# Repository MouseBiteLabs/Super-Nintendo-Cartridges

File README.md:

# Super Nintendo Game Cartridges

This is a repository listing all of my Super Nintendo Cartridge board variants. These *do not* include variants with special chips, such as SA-1 or the Super Game Boy boards. This repository is for the "standard" mapping types.

Use the following table (or navigate the above folders) for information on each specific baord type. <a href="https://github.com/MouseBiteLabs/Super-Nintendo-Cartridges/wiki">Please also review the wiki for more information.</a>

Note that the boards listed below are planned for development. No dates for upload are guaranteed.

## SNES Board Variants

| **Board Name**                                                                                                     | **Board Number**   | **Max ROM Size** | **Max RAM Size** | **Mappings Supported**         | **Multicart Support?**            | **Memory Family Used** |
|--------------------------------------------------------------------------------------------------------------------|--------------------|------------------|------------------|--------------------------------|-----------------------------------|------------------------|
| <a href="https://github.com/MouseBiteLabs/Super-Nintendo-Cartridges/tree/main/Advanced%20Flash">Advanced Flash</a> | SNES-8XJ4D-01A     | 8 MB             | 32 KB            | LoROM, HiROM, ExLoROM, ExHiROM | Yes (2 games; 4MB ROM, 32KB RAM)  | Type A (M29F160)       |
| <a href="https://github.com/MouseBiteLabs/Super-Nintendo-Cartridges/tree/main/LoROM%20Flash">LoROM Flash</a>       | SNES-8XL8D-01A     | 8 MB             | 128 KB           | LoROM, ExLoROM                 | Yes (2 games; 4MB ROM, 32KB RAM)  | Type A (M29F160)       |
| <a href="https://github.com/MouseBiteLabs/Super-Nintendo-Cartridges/tree/main/HiROM%20Flash">HiROM Flash</a>       | SNES-8XH8D-01A     | 8 MB             | 128 KB           | HiROM, ExHiROM                 | Yes (2 games; 4MB ROM, 32KB RAM)  | Type A (M29F160)       |
| <a href="https://github.com/MouseBiteLabs/Super-Nintendo-Cartridges/tree/main/Advanced%20UV">Advanced UV</a>       | SNES-8XJ8D-01C     | 8 MB             | 128 KB           | LoROM, HiROM, ExLoROM, ExHiROM | Yes (2 games; 4MB ROM, 32KB RAM)  | Type C (27C322)        |
| <a href="https://github.com/MouseBiteLabs/Super-Nintendo-Cartridges/tree/main/Basic%20UV">Basic UV</a>             | SNES-4NJ8D-01C     | 4 MB             | 128 KB           | LoROM, HiROM                   | No                                | Type C (27C160)        |
| <a href="https://github.com/MouseBiteLabs/Super-Nintendo-Cartridges/tree/main/SA-1">SA-1</a>                       | SNES-4SA8S-01C     | 4 MB             | 128 KB           | N/A                            | No                                | Type C (27C322)        |

## Naming Convention

| SNES                                | \- | 8                 | X               | J              | 4            | D                                    | \- | 01       | A                                       |
| ----------------------------------- | -- | ----------------- | --------------- | -------------- | ------------ | ------------------------------------ | -- | -------- | --------------------------------------- |
| Super Nintendo Entertainment System |    | Max ROM Size (MB) | Ex Mode Support | Mapper Type(s) | Max RAM Size | Multicart Support                    |    | Revision | Memory Family                           |
|                                     |    | 1                 | N = No          | L = LoROM      | 0 = None     | S = Single game                      |    |          | A = New EEPROM (M29F160)                |
|                                     |    | 2                 | X = Yes         | H = HiROM      | 1 = 2 KB     | D = Multicart (split max ROM space)  |    |          | B = NOS EEPROM (29F016, 29F032, 29F033) |
|                                     |    | 4                 |                 | J = Both       | 2 = 8 KB     | M = Multicart (double max ROM space) |    |          | C = UV EPROMs (27C160, 27C322, etc)     |
|                                     |    | 6                 | SA =            | SA1            | 4 = 32 KB    |                                      |    |          |                                         |
|                                     |    | 8                 |                 |                | 8 = 128 KB   |                                      |    |          |                                         |

## License

<br />This work is licensed under a <a rel="license" href="http://creativecommons.org/licenses/by-sa/4.0/">Creative Commons Attribution-ShareAlike 4.0 International License</a>. You are able to copy and redistribute the material in any medium or format, as well as remix, transform, or build upon the material for any purpose (even commercial) - but you **must** give appropriate credit, provide a link to the license, and indicate if any changes were made.

©MouseBiteLabs 2024

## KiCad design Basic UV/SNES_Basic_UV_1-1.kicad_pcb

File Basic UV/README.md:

# Super Nintendo Basic UV Cartridge (SNES-4NJ8D-01C) 

# Order at your own risk -- v1.1 is untested

This is an updated design of my old <a href="https://mousebitelabs.com/2019/08/12/how-to-make-a-snes-reproduction-cartridge-quick-guide/">SNES Basic cartridge boards</a>, which can use the original mask ROM chips from SNES carts, or the older 27C160 UV EPROM chips. You can even use my <a href="https://github.com/MouseBiteLabs/ROM-Adapter-Boards/tree/main/29F160%20to%20UV%20EPROM">29F160 to 27C160 adapter boards</a>, which use brand new 29F160 flash chips if you don't want to deal with old parts. 

Functionally, this design is the same as the older one, but under the hood I have ported the project over from Eagle to KiCad, and heavily cleaned up the schematic and some of the trace routings. I also added support for the MAD-1 chip from a donor board, unlocking a lot of potential for replacing old or damaged games. This version is also fully open source.

This cartridge covers a large portion of the SNES library, capable of any standard cartridge **but not those with co-processors, such as SA-1 or SuperFX.** You can backup games onto it with the following settings:
- HiROM and LoROM memory maps
- Up to 4 MB of ROM space
- Up to 128 KB of RAM space

All gerbers and source files can be found in this repo, as again, this project is fully open source. Please read all instructions before attempting the project.

## Important Things Before You Start

1) <a href="https://github.com/MouseBiteLabs/Super-Nintendo-Cartridges/wiki">Please review the wiki for more information about using the circuit boards, instructions for how to program them, and example builds.</a>
2) When soldering parts on, it's a good idea to put kapton tape or otherwise cover the bottom cartridge edge. You do not want to get solder on the cartridge contacts.
3) I am not responsible for any damage you do to your self or your property. Attempt this project at your own risk.
4) I do not guarantee design compatibility. You may encounter issues with certain games. There is also a chance I have made an error in the design or the BOM - if this is the case, I will do everything I can to address the problem as quickly as possible.
5) If you are using this board to make games other than for personal use, you must have permission from the originator to use and distribute any ROM images or other related material. You are responsible for making sure you adhere to any license requirements.

DO NOT use my circuit boards for profiting from stolen work - this especially includes homebrew content, ROM hacks, and using fan-made labels without permission from the originator. **Support ALL original creators!**

## Board Characteristics and Order Information

The zipped folder contains all the gerber files for this board. The following options **must** be chosen when ordering boards for yourself.

- Thickness: 1.2mm
- Surface Finish: ENIG
- Gold Fingers: Yes, 30° chamfer

You can use the zipped folder at any board fabricator you like. You may also buy the board from PCBWay using this link (disclosure: I receive 10% of the sale value to go towards future PCB orders of my own):

### Purchase from My Website

You can purchase this circuit board at my website, [https://mousebitelabs.store](https://mousebitelabs.store). Click the following image to be directed to the specific item listing:

### Purchase from Etsy

I also offer the board on Etsy, if you would rather purchase through there - click the banner to be redirected.

## Required Equipment

- You will need basic tools, like a soldering iron.
- If you are using this board with any OEM parts, like the CIC or MAD-1 or even a full replacement cartridge, you will... need that cartridge.
- If you are not using an original ROM chip, you need a way to program the new ROM chip. There are a few ways I have programmed them in the past:
  - You can use the <a href="https://xgecu.myshopify.com/products/xgecu-new-t48-tl866-3gprogrammer-v12-01-support-28000-ics-for-spi-nor-nand-flash-emmc-bga153-162-169-100-221-tsop-sop-plcc">T48 programmer</a> to program 27C801 or equivalent 1MB UV EPROMs for U3.
  - Using the T48 programmer with my <a href="https://github.com/MouseBiteLabs/27C322-TL866-Adapter">27C322 to TL866 Programming Adatper</a> board allows you to program 27C160 UV EPROMs.
  - The <a href="https://www.mcumall.com/store/index.php?route=product/product&path=66&product_id=85">GQ4x4 programmer</a> (and the ZIF adapter board that comes with it) can also be used to program UV EPROMs.
  - The T48 programmer with the <a href="https://xgecu.myshopify.com/products/100-original-xgecu-adp_f48_ex-1-tsop48-special-adapter-for-nor-flash-only-use-on-t48-tl866-3g-programmer">TSOP48 adapter</a> can be used to program 29F160 chips on my <a href="https://github.com/MouseBiteLabs/ROM-Adapter-Boards/tree/main/29F160%20to%20UV%20EPROM">29F160 to 27C160 adapter boards</a> placed in the U4 socket, or to program 29F016 chips on my <a href="https://github.com/MouseBiteLabs/ROM-Adapter-Boards/tree/main/SNES%20to%20TSOP">29F016 to SNES adapter boards</a> placed in the U3 socket.
  - If you are using the <a href="https://github.com/MouseBiteLabs/ROM-Adapter-Boards/tree/main/29F160%20to%20UV%20EPROM">29F160 to 27C160 adapter board</a>, and you install it into U4 along with the pin to connect /WE between the adapter and the cartridge, you can use the <a href="https://github.com/sanni/cartreader">OSCR</a> to load the game and save data onto the catridge, after the cartridge is assembled.
- This cartridge uses the PIC12F629 with the <a href="https://sd2snes.de/blog/cool-stuff/supercic">SuperCIC code</a> to fake out the lockout chip. You will need a way to program these PIC chips. I use the T48 to do so, but you can also use something like the <a href="https://www.microchip.com/en-us/development-tool/pg164130">PICkit 3.</a> Note that if you have region modded your SNES, you won't need the lockout chips in the cartridges.

## How to Program

<a href="https://github.com/MouseBiteLabs/Super-Nintendo-Cartridges/wiki/Preparing-the-ROM">Please check out the wiki pages on how to prepare the ROM and program the cartridge.</a>

### Important note for 27C801

If you are using a UV EPROM in the U3 socket (likely the 27C801), then the ROM file you load onto the chip must be swapbinned. This is covered in the wiki link above.

## Board Configurations

This board is highly customizable. You *do not* need every single part on this board to make a game. The game you want to make is mainly dependent on the memory mapping (LoROM/HiROM), the ROM size, and the RAM size. Depending on your needs, you only need to solder on certain components, which you can find below in the BOM section. You will also need to configure the game with the various solder jumpers on the back of the board.

<a href="https://github.com/MouseBiteLabs/Super-Nintendo-Cartridges/wiki/Basic-UV">**I highly recommend checking out the various examples of board configurations on the wiki.**</a>

### Components Required

I've split up the requisite parts into a few different "Groups" which you can find a comprehensive list for in the BOM section a few sections down from this one.

- **Every board needs Group A components.** You can make games that have no RAM and are up to 4 MB large with this configuration.
- If you need battery-backed RAM, **add Group B components.** This will add up to 128 KB of RAM space. You will then need to add either...
  - **Group C components** if you are using the 74HCT139 decoder chip (which does not require a donor cartridge),
 
  OR
  
  - **Group D components** if you are using the MAD-1 mapper (which requires a donor cartridge).

Along with these groups, please also follow the configurations detailed in the following sections.

### The Lockout Chip

There are two sockets and two capacitors labeled "U2" and "C2," respectively. Only populate ONE set of these. Do not populate both. The 16-pin socket is for the original CIC chip from a donor cartridge, and the 8-pin socket is for the SuperCIC clone chip using the PIC12F629 that you have to program yourself. If your SNES is modded to be region-unlocked, then you don't need either of these chips.

### Hi/Lo Socket Selection

If your game is the LoROM mapping type, solder U3 or U4 in the bottom set of sockets (labeled "LO" on the left side) and, if necessary, U6L or U8L. If your game is of the HiROM mapping type, solder U3 or U4 in the top set of sockets (labeled "HI" on the left side) and, if necessary, U6H or U8H.

### Mapper Bypass Solder Jumper

This is the only set of solder jumper pads on the front of the board. If your game does not use SRAM, then you must solder these pads together. **Do not solder these pads if your game uses SRAM.**

### LoRom/HiROM Solder Jumpers

For these 3-segment pads, use a solder bridge on the middle pad to either side depending on the option you need. There are a handful of them across the board, and not all of them are necessary for you to set - though, importantly, if you want to take the guesswork out of it, **you can configure all of them without any ill side effects** to make it simpler.

1) The one Lo/Hi jumper on the bottom left of the board, behind U3, only need to be set if you have a ROM in the U3 socket.
2) The two Lo/Hi jumpers on the right side, behind U6L and U6H (the MAD-1s), only need to be set if you are using U8L or U8L (the 74HCT139s)
3) The four Lo/Hi jumpers at the top of the board only need to be set if you are using SRAM on the board
4) The one Lo/Hi jumper in the middle of the board behind U4 only needs to be set if you are using the <a href="https://github.com/MouseBiteLabs/ROM-Adapter-Boards/tree/main/29F160%20to%20UV%20EPROM">29F160 to 27C160 adapter boards</a> in the U4 socket

### SRAM Size

The set of pads at the top left underneath the SRAM chip configure the size of the SRAM that the SNES will see. All pads must be configured if you are using SRAM, and each set of 2 should be soldered in the same direction. The example picture below shows a game configured for 256 Kbit of SRAM. **It is important to note these numbers represent the SRAM in BITS, not BYTES. To figure out the BYTES of SRAM, take the numbers here and divide by 8.**

### U4 Configuration Pads

These two sets of 3-way jumpers only need to be set if you have something populated in U4. Solder the middle pads to the left if you are using a 27C160 UV EPROM, or solder the middle pads to the right if you are using my <a href="https://github.com/MouseBiteLabs/ROM-Adapter-Boards/tree/main/29F160%20to%20UV%20EPROM">29F160 to 27C160 adapter boards</a>.

(Remember: the LoROM/HiROM pads to the right of these do not need to be set if you are using the 27C160.)

## Estimating Battery Life

To accurately estimate the battery life, measure the voltage across R1 using a multimeter in DC mV mode, touching the probes to the two test point pads on either side of R1. You should read something around 1 mV or less. If you are severely higher than 10 mV, like in the 100's of mV, then you have a problem on your board.

Once you have a suitable voltage, find the milliamp-hour rating of your selected battery (preferrably from a datasheet). For example, a Renata CR2032 battery is rated for 225 mAh.

Now to estimate battery life, take the voltage measurement in mV and the battery rating in mAh, and plug it into this equation: 

Time (years) = Resistance of R1 (ohms) * Battery capacity (mAh) / Voltage (mV) / 8760

The factor of 8760 is for converting years to hours (24 hours in a day, 365 days in a year). The resistance of R1 is 1000 ohms. So for an example, if you measured 1 mV on R1 and are using a Renata CR2032, you would get 1000 * 225 / 1 / 8760 = **25.7 years.**

## Troubleshooting

<a href="https://github.com/MouseBiteLabs/Super-Nintendo-Cartridges/wiki/Troubleshooting-Tips">Please check out the wiki pages for troubleshooting tips.</a>

## Bill of Materials (BOM)

The component groups required for the build you want to make are detailed above.

### Group A - Up to 4 MB ROM, No RAM

In the following table, choose **one** of the options for U2.

| Reference | Value/Part Number | Package              | Description                     | Source                                           |
| --------- | ----------------- | -------------------- | ------------------------------- | ------------------------------------------------ |
| C1        | 22u               | Radial 2.5mm spacing | Aluminum Electrolytic Capacitor | [https://mou.sr/4lzfiK1](https://mou.sr/4lzfiK1) |
| C2        | 0.1u              | Radial 2.5mm spacing | Ceramic Capacitor               | [https://mou.sr/481ILov](https://mou.sr/481ILov) |
| U2        | CIC               | DIP-16               | Region Lockout Chip             | Donor cartridge                                  |
| U2        | PIC12F629         | DIP-8                | PIC Microcontroller             | [https://mou.sr/3XuEZzO](https://mou.sr/3XuEZzO) |
| U2        | PIC12F629         | SOIC-8               | PIC Microcontroller             | [https://mou.sr/4dSUh90](https://mou.sr/4dSUh90) |

In the following table, choose **one** of the following options for U3 or U4. If you use a part in U3, then populate C3. If you use a part in U4, populate C4.

| Reference | Value/Part Number      | Package              | Description              | Source                                                                                                                                                                           |
| --------- | ---------------------- | -------------------- | ------------------------ | -------------------------------------------------------------------------------------------------------------------------------------------------------------------------------- |
| C3        | 0.1u                   | Radial 2.5mm spacing | Ceramic Capacitor        | [https://mou.sr/481ILov](https://mou.sr/481ILov)                                                                                                                                 |
| C4        | 0.1u                   | Radial 2.5mm spacing | Ceramic Capacitor        | [https://mou.sr/481ILov](https://mou.sr/481ILov)                                                                                                                                 |
| U3        | Mask ROM               | DIP-32/DIP-36        | Original SNES Mask ROM   | Donor Cartridge                                                                                                                                                                  |
| U3        | 27C801                 | DIP-32               | UV EPROM                 | AliExpress, eBay                                                                                                                                                                 |
| U3        | SNES-to-TSOP PCB       | DIP-36               | Adapter board for 29F016 | [https://github.com/MouseBiteLabs/ROM-Adapter-Boards/tree/main/SNES%20to%20TSOP](https://github.com/MouseBiteLabs/ROM-Adapter-Boards/tree/main/SNES%20to%20TSOP)                 |
| U4        | 27C160                 | DIP-42               | UV EPROM                 | AliExpress, eBay                                                                                                                                                                 |
| U4        | 29F160 to UV EPROM PCB | DIP-42               | Adapter board for 29F160 | [https://github.com/MouseBiteLabs/ROM-Adapter-Boards/tree/main/29F160%20to%20UV%20EPROM](https://github.com/MouseBiteLabs/ROM-Adapter-Boards/tree/main/29F160%20to%20UV%20EPROM) |

### Group B - adds 32 KB of RAM

| Reference | Value/Part Number | Package              | Description                     | Source                                           |
| --------- | ----------------- | -------------------- | ------------------------------- | ------------------------------------------------ |
| B1        | CR2032            | CR2032               | Coin Cell Battery               | [https://mou.sr/3Wj2m0G](https://mou.sr/3Wj2m0G) |
| CB        | 22u               | Radial 2.5mm spacing | Aluminum Electrolytic Capacitor | [https://mou.sr/4lzfiK1](https://mou.sr/4lzfiK1) |
| C5        | 0.1u              | Radial 2.5mm spacing | Ceramic Capacitor               | [https://mou.sr/481ILov](https://mou.sr/481ILov) |
| R1        | 1k                | Axial                | Resistor                        | [https://mou.sr/4hYkrZr](https://mou.sr/4hYkrZr) |
| U5        | AS6C62256         | DIP-28               | SRAM                            | [https://mou.sr/3HlZ0mh](https://mou.sr/3HlZ0mh) |

### Group B (Optional) - adds 128 KB of RAM (instead of 32 KB)

Replace U5 in Group B above with the part detailed here, and add the other three components. **I personally recommend sticking to the AS6C62256 SRAM chip unless you absolutely need more RAM space.**

| Reference | Value/Part Number | Package | Description | Source                                           |
| --------- | ----------------- | ------- | ----------- | ------------------------------------------------ |
| Q2        | 2N3904            | TO-92-3 | NPN BJT     | [https://mou.sr/3HlkU91](https://mou.sr/3HlkU91) |
| R6        | 100k              | Axial   | Resistor    | [https://mou.sr/3Ib4SgO](https://mou.sr/3Ib4SgO) |
| R7        | 10k               | Axial   | Resistor    | [https://mou.sr/42AN0WU](https://mou.sr/42AN0WU) |
| U5        | AS6C1008          | DIP-32  | SRAM        | [https://mou.sr/3hNkGxg](https://mou.sr/3hNkGxg) |

### Group C - adds supporting circuitry for battery backed RAM (no donor cart)

| Reference | Value/Part Number | Package              | Description       | Source                                                   |
| --------- | ----------------- | -------------------- | ----------------- | -------------------------------------------------------- |
| C8        | 0.1u              | Radial 2.5mm spacing | Ceramic Capacitor | [https://mou.sr/481ILov](https://mou.sr/481ILov)         |
| D1        | BAT85             | DO-35-2              | Schottky Diode    | [https://mou.sr/49GVT4m](https://mou.sr/49GVT4m)         |
| D2        | BAT85             | DO-35-2              | Schottky Diode    | [https://mou.sr/49GVT4m](https://mou.sr/49GVT4m)         |
| D3        | BAT85             | DO-35-2              | Schottky Diode    | [https://mou.sr/49GVT4m](https://mou.sr/49GVT4m)         |
| Q1        | 2N3904            | TO-92-3 / SOT-23-3   | NPN BJT           | THT: https://mou.sr/3HlkU91, SMT: https://mou.sr/3C8piaZ |
| R2        | 100k              | Axial                | Resistor          | [https://mou.sr/3Ib4SgO](https://mou.sr/3Ib4SgO)         |
| R3        | 10k               | Axial                | Resistor          | [https://mou.sr/42AN0WU](https://mou.sr/42AN0WU)         |
| R4        | 1k                | Axial                | Resistor          | [https://mou.sr/4hYkrZr](https://mou.sr/4hYkrZr)         |
| R5        | 10k               | Axial                | Resistor          | [https://mou.sr/42AN0WU](https://mou.sr/42AN0WU)         |
| U8        | 74HCT139          | DIP-16               | Decoder           | [https://mou.sr/441VXuJ](https://mou.sr/441VXuJ)         |

### Group D - adds supporting circuitry for battery backed RAM (donor cart)

| Reference | Value/Part Number | Package              | Description            | Source                                           |
| --------- | ----------------- | -------------------- | ---------------------- | ------------------------------------------------ |
| C6        | 0.1u              | Radial 2.5mm spacing | Ceramic Capacitor      | [https://mou.sr/481ILov](https://mou.sr/481ILov) |
| U6        | MAD-1             | DIP-16               | Memory Address Decoder | Donor Cartridge                                  |

## Restrictions for v1.0

If you have a v1.0 board, you have the following restrictions:

- Only a replacement CIC chip with the PIC12F629 can be used
- MAD-1 is not supported (the wiring is wrong)
- If you are using a 27C160 EPROM in U4, you must bend up pin 32 and separately wire it to a GND point (like pin 31 on the EPROM)

## Revision History

### v1.1 - Release

- Fix OEM CIC wiring
- Fix MAD-1 wiring
- Add jumpers and extra pins for 29F160 Adapter board support

### v1.0 - Prototype

- Release of the KiCad-ported version of my original SNES Basic cart design
- Removed the "SRAM Enable" pads and made the SRAM always enabled
- Added MAD-1 support to the board

## Acknowledgements

- Continual thanks to all in the nesdev community for their resources, design tips, and support throughout the past half-decade. This design was one of my original ones that was improved through their help and feedback when I was first starting out.

## License

<br />This work is licensed under a <a rel="license" href="http://creativecommons.org/licenses/by-sa/4.0/">Creative Commons Attribution-ShareAlike 4.0 International License</a>. You are able to copy and redistribute the material in any medium or format, as well as remix, transform, or build upon the material for any purpose (even commercial) - but you **must** give appropriate credit, provide a link to the license, and indicate if any changes were made.

©MouseBiteLabs 2025

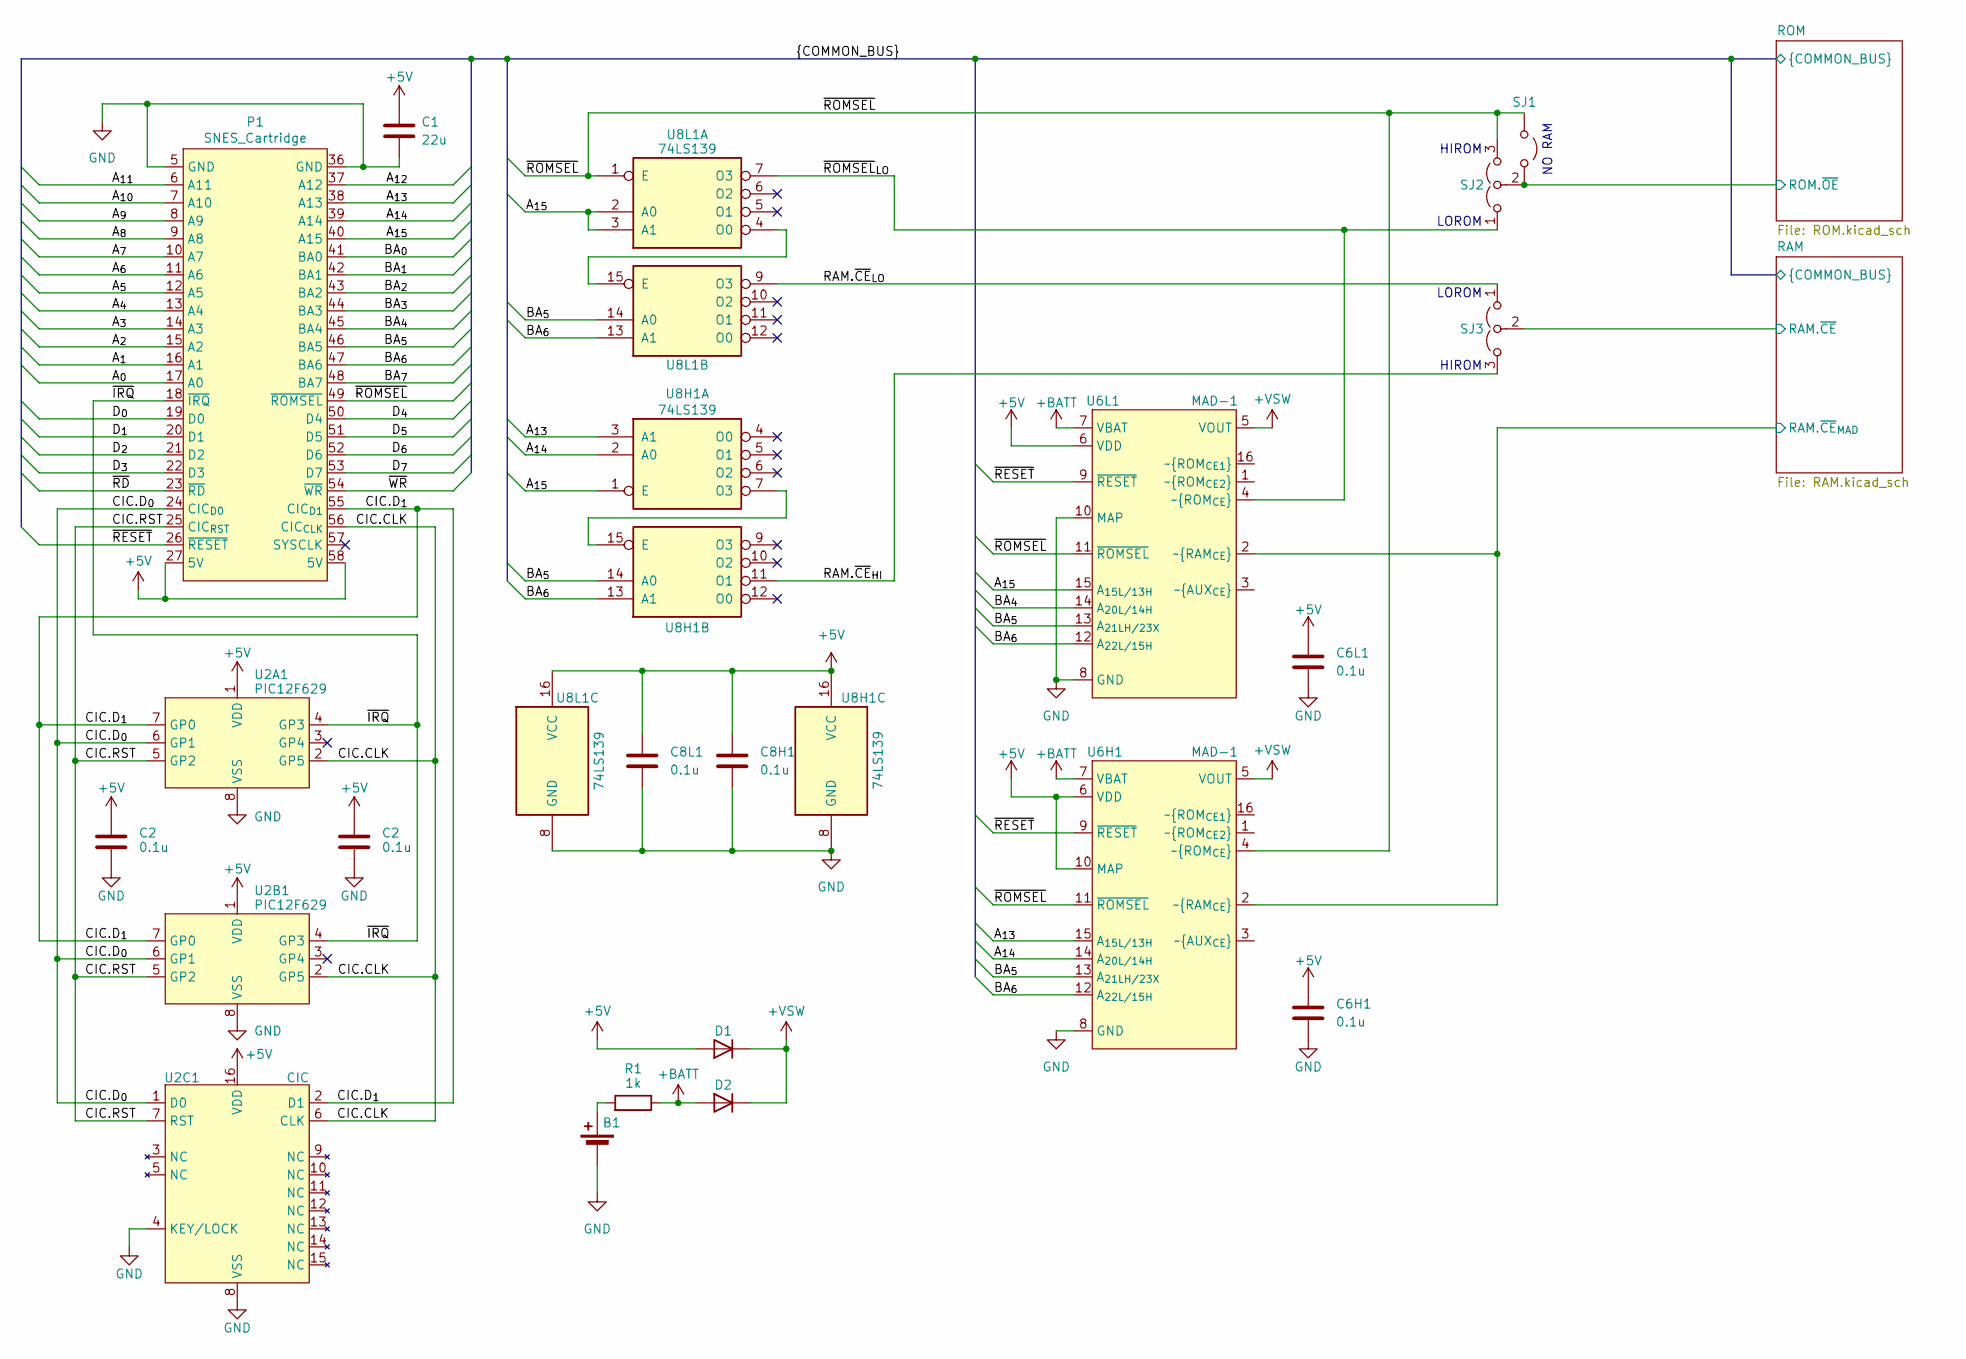
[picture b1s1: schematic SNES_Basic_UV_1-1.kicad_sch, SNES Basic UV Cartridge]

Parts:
B1: CR2025; COIN_CELL
C1: 22u; CP_Radial_D5.0mm_P2.50mm
C2, C6H1, C6L1, C8H1, C8L1: 0.1u; C_THT
D1, D2: D; DIODE_THT_SMT
P1: SNES_Cartridge; Cart_Edge_SNES_Standard
R1: 1k; THT_SMT_0803
SJ1: Jumper_2_Open; SJ
SJ2, SJ3: Jumper_3_Open; SJ_2
U2A1: PIC12F629; SOIC-8_3.9x4.9mm_P1.27mm
U2B1: PIC12F629; DIP-8_W7.62mm
U2C1: CIC; DIP-16_W7.62mm
U6H1, U6L1: MAD-1; DIP-16_W7.62mm
U8H1, U8L1: 74LS139; DIP-16_W7.62mm

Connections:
+5V: C1.1, C2.1, C6H1.1, C6L1.1, C8H1.1, C8L1.1, D1.2 (A), P1.27 (5V), P1.58 (5V), U2A1.1 (VDD), U2B1.1 (VDD), U2C1.16 (VDD), U6H1.6 (VDD), U6H1.10 (MAP), U6L1.6 (VDD), U8H1.16 (VCC), U8L1.16 (VCC); also elsewhere on the board
+BATT: D2.2 (A), R1.1, U6H1.7 (VBAT), U6L1.7 (VBAT)
+VSW: D1.1 (K), D2.1 (K), U6H1.5 (VOUT), U6L1.5 (VOUT); also elsewhere on the board
/A_{0}: P1.17 (A0); also elsewhere on the board
/A_{1}: P1.16 (A1); also elsewhere on the board
/A_{2}: P1.15 (A2); also elsewhere on the board
/A_{3}: P1.14 (A3); also elsewhere on the board
/A_{4}: P1.13 (A4); also elsewhere on the board
/A_{5}: P1.12 (A5); also elsewhere on the board
/A_{6}: P1.11 (A6); also elsewhere on the board
/A_{7}: P1.10 (A7); also elsewhere on the board
/A_{8}: P1.9 (A8); also elsewhere on the board
/A_{9}: P1.8 (A9); also elsewhere on the board
/A_{10}: P1.7 (A10); also elsewhere on the board
/A_{11}: P1.6 (A11); also elsewhere on the board
/A_{12}: P1.37 (A12); also elsewhere on the board
/A_{13}: P1.38 (A13), U6H1.15 (A_{15L/13H}), U8H1.3 (A1); also elsewhere on the board
/A_{14}: P1.39 (A14), U6H1.14 (A_{20L/14H}), U8H1.2 (A0); also elsewhere on the board
/A_{15}: P1.40 (A15), U6L1.15 (A_{15L/13H}), U8H1.1 (E), U8L1.2 (A0), U8L1.3 (A1); also elsewhere on the board
/BA_{0}: P1.41 (BA0); also elsewhere on the board
/BA_{1}: P1.42 (BA1); also elsewhere on the board
/BA_{2}: P1.43 (BA2); also elsewhere on the board
/BA_{3}: P1.44 (BA3); also elsewhere on the board
/BA_{4}: P1.45 (BA4), U6L1.14 (A_{20L/14H}); also elsewhere on the board
/BA_{5}: P1.46 (BA5), U6H1.13 (A_{21LH/23X}), U6L1.13 (A_{21LH/23X}), U8H1.14 (A0), U8L1.14 (A0); also elsewhere on the board
/BA_{6}: P1.47 (BA6), U6H1.12 (A_{22L/15H}), U6L1.12 (A_{22L/15H}), U8H1.13 (A1), U8L1.13 (A1); also elsewhere on the board
/BA_{7}: P1.48 (BA7); also elsewhere on the board
/CIC.CLK: P1.56 (CIC_{CLK}), U2A1.2 (GP5), U2B1.2 (GP5), U2C1.6 (CLK)
/CIC.D_{0}: P1.24 (CIC_{D0}), U2A1.6 (GP1), U2B1.6 (GP1), U2C1.1 (D0)
/CIC.D_{1}: P1.55 (CIC_{D1}), U2A1.7 (GP0), U2B1.7 (GP0), U2C1.2 (D1)
/CIC.RST: P1.25 (CIC_{RST}), U2A1.5 (GP2), U2B1.5 (GP2), U2C1.7 (RST)
/D_{0}: P1.19 (D0); also elsewhere on the board
/D_{1}: P1.20 (D1); also elsewhere on the board
/D_{2}: P1.21 (D2); also elsewhere on the board
/D_{3}: P1.22 (D3); also elsewhere on the board
/D_{4}: P1.50 (D4); also elsewhere on the board
/D_{5}: P1.51 (D5); also elsewhere on the board
/D_{6}: P1.52 (D6); also elsewhere on the board
/D_{7}: P1.53 (D7); also elsewhere on the board
/RAM.~CE_{HI}: SJ3.3 (B), U8H1.11 (O1)
/RAM.~CE_{LO}: SJ3.1 (A), U8L1.9 (O3)
/RAM/RAM.~CE: SJ3.2 (C); also elsewhere on the board
/RAM/~CE_{SRAM}: U6H1.2 (~RAM_{CE}), U6L1.2 (~RAM_{CE}); also elsewhere on the board
/ROM/ROM.~OE: SJ1.1 (A), SJ2.2 (C); also elsewhere on the board
/~IRQ: P1.18 (~IRQ), U2A1.4 (GP3), U2B1.4 (GP3)
/~RD: P1.23 (~RD); also elsewhere on the board
/~RESET: P1.26 (~RESET), U6H1.9 (~RESET), U6L1.9 (~RESET); also elsewhere on the board
/~ROMSEL: P1.49 (~ROMSEL), SJ1.2 (B), SJ2.3 (B), U6H1.4 (~ROM_{CE}), U6H1.11 (~ROMSEL), U6L1.11 (~ROMSEL), U8L1.1 (E)
/~ROMSEL_{LO}: SJ2.1 (A), U6L1.4 (~ROM_{CE}), U8L1.7 (O3)
/~WR: P1.54 (~WR); also elsewhere on the board
GND: B1.2 (-), C1.2, C2.2, C6H1.2, C6L1.2, C8H1.2, C8L1.2, P1.5 (GND), P1.36 (GND), U2A1.8 (VSS), U2B1.8 (VSS), U2C1.4 (KEY/LOCK), U2C1.8 (VSS), U6H1.8 (GND), U6L1.8 (GND), U6L1.10 (MAP), U8H1.8 (GND), U8L1.8 (GND); also elsewhere on the board
unnamed: B1.1 (+), R1.2
unnamed: U8H1.7 (O3), U8H1.15 (E)
unnamed: U8L1.4 (O0), U8L1.15 (E)

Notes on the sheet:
HIROM LOROM
NO RAM
LOROM HIROM

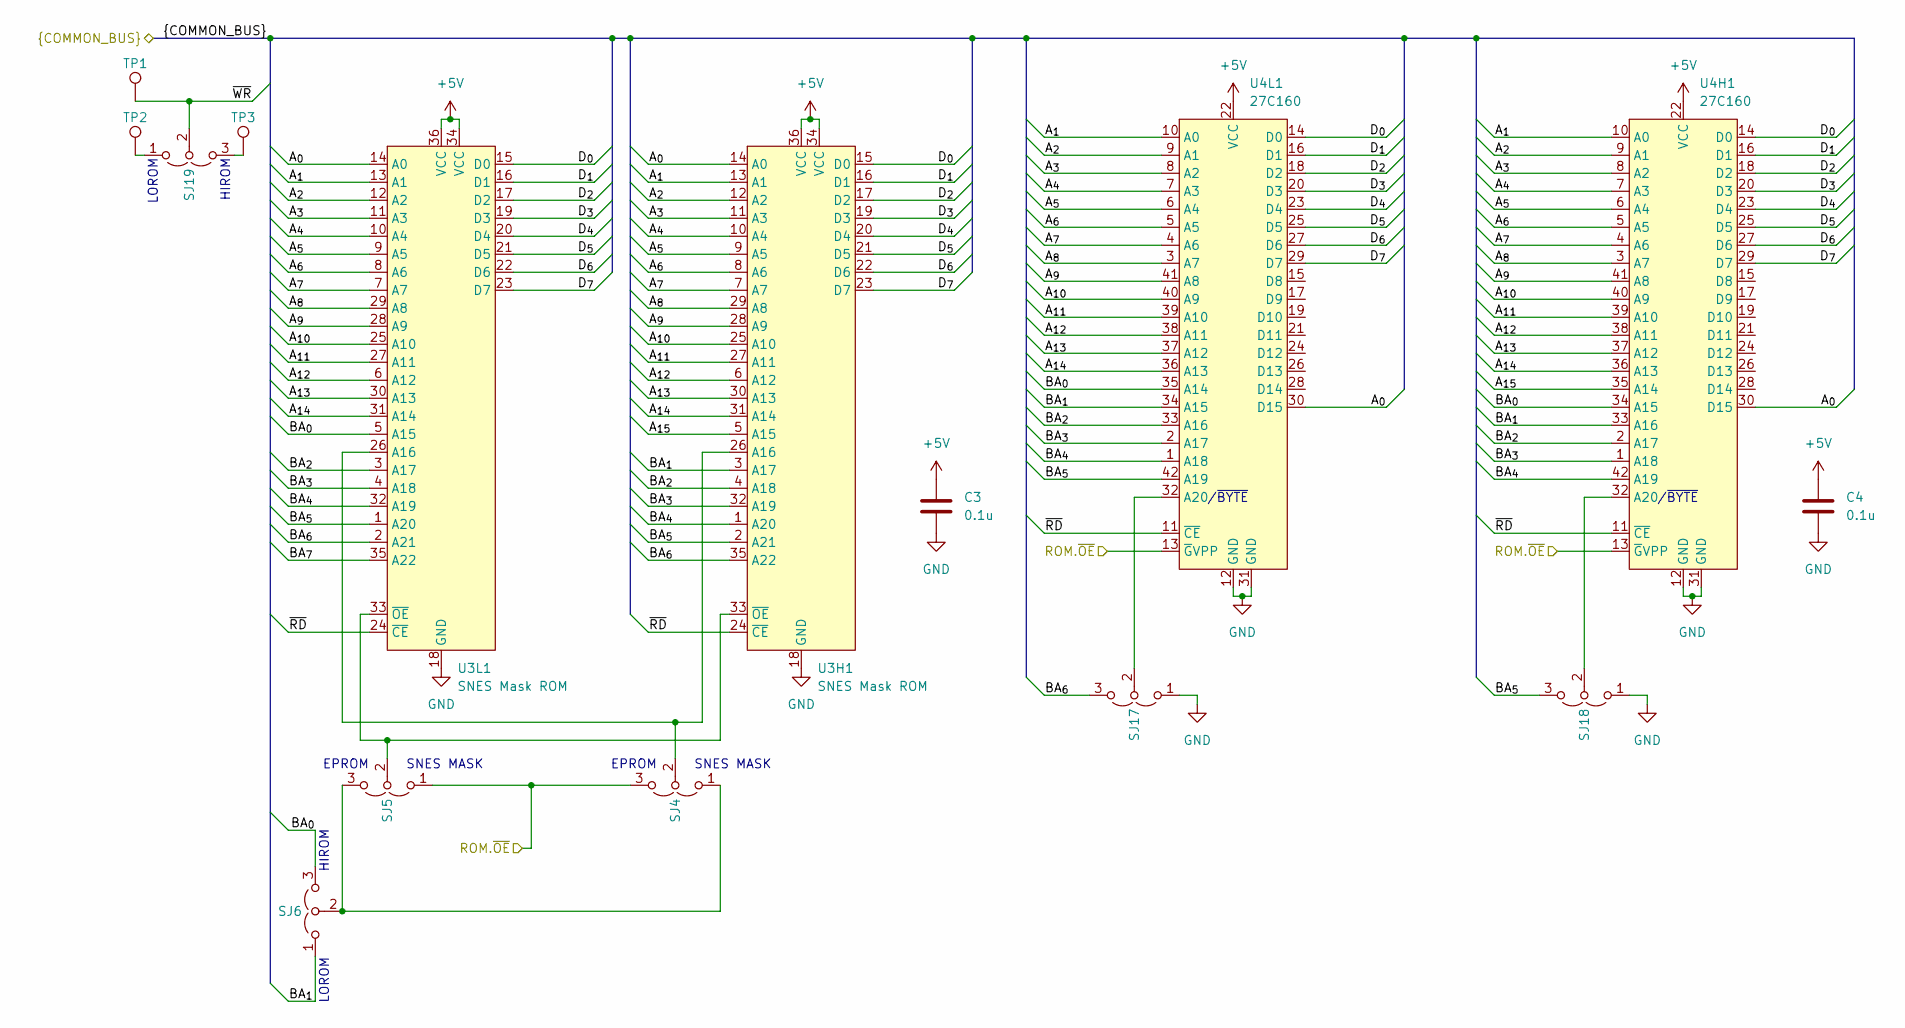
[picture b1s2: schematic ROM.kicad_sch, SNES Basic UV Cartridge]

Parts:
C3, C4: 0.1u; C_THT
SJ4, SJ5, SJ6, SJ17, SJ18, SJ19: Jumper_3_Open; SJ_2
TP1, TP2, TP3: TPB1,27; TestPoint_THTPad_D1.5mm_Drill0.7mm
U3H1, U3L1: SNES Mask ROM; 36-PDIP_SLIM
U4H1, U4L1: 27C160; DIP-42_W15.24mm

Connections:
+5V: C3.1, C4.1, U3H1.34 (VCC), U3H1.36 (VCC), U3L1.34 (VCC), U3L1.36 (VCC), U4H1.22 (VCC), U4L1.22 (VCC); also elsewhere on the board
/A_{0}: U3H1.14 (A0), U3L1.14 (A0), U4H1.30 (D15), U4L1.30 (D15); also elsewhere on the board
/A_{1}: U3H1.13 (A1), U3L1.13 (A1), U4H1.10 (A0), U4L1.10 (A0); also elsewhere on the board
/A_{2}: U3H1.12 (A2), U3L1.12 (A2), U4H1.9 (A1), U4L1.9 (A1); also elsewhere on the board
/A_{3}: U3H1.11 (A3), U3L1.11 (A3), U4H1.8 (A2), U4L1.8 (A2); also elsewhere on the board
/A_{4}: U3H1.10 (A4), U3L1.10 (A4), U4H1.7 (A3), U4L1.7 (A3); also elsewhere on the board
/A_{5}: U3H1.9 (A5), U3L1.9 (A5), U4H1.6 (A4), U4L1.6 (A4); also elsewhere on the board
/A_{6}: U3H1.8 (A6), U3L1.8 (A6), U4H1.5 (A5), U4L1.5 (A5); also elsewhere on the board
/A_{7}: U3H1.7 (A7), U3L1.7 (A7), U4H1.4 (A6), U4L1.4 (A6); also elsewhere on the board
/A_{8}: U3H1.29 (A8), U3L1.29 (A8), U4H1.3 (A7), U4L1.3 (A7); also elsewhere on the board
/A_{9}: U3H1.28 (A9), U3L1.28 (A9), U4H1.41 (A8), U4L1.41 (A8); also elsewhere on the board
/A_{10}: U3H1.25 (A10), U3L1.25 (A10), U4H1.40 (A9), U4L1.40 (A9); also elsewhere on the board
/A_{11}: U3H1.27 (A11), U3L1.27 (A11), U4H1.39 (A10), U4L1.39 (A10); also elsewhere on the board
/A_{12}: U3H1.6 (A12), U3L1.6 (A12), U4H1.38 (A11), U4L1.38 (A11); also elsewhere on the board
/A_{13}: U3H1.30 (A13), U3L1.30 (A13), U4H1.37 (A12), U4L1.37 (A12); also elsewhere on the board
/A_{14}: U3H1.31 (A14), U3L1.31 (A14), U4H1.36 (A13), U4L1.36 (A13); also elsewhere on the board
/A_{15}: U3H1.5 (A15), U4H1.35 (A14); also elsewhere on the board
/BA_{0}: SJ6.3 (B), U3L1.5 (A15), U4H1.34 (A15), U4L1.35 (A14); also elsewhere on the board
/BA_{1}: SJ6.1 (A), U3H1.3 (A17), U4H1.33 (A16), U4L1.34 (A15); also elsewhere on the board
/BA_{2}: U3H1.4 (A18), U3L1.3 (A17), U4H1.2 (A17), U4L1.33 (A16); also elsewhere on the board
/BA_{3}: U3H1.32 (A19), U3L1.4 (A18), U4H1.1 (A18), U4L1.2 (A17); also elsewhere on the board
/BA_{4}: U3H1.1 (A20), U3L1.32 (A19), U4H1.42 (A19), U4L1.1 (A18); also elsewhere on the board
/BA_{5}: SJ18.3 (B), U3H1.2 (A21), U3L1.1 (A20), U4L1.42 (A19); also elsewhere on the board
/BA_{6}: SJ17.3 (B), U3H1.35 (A22), U3L1.2 (A21); also elsewhere on the board
/BA_{7}: U3L1.35 (A22); also elsewhere on the board
/D_{0}: U3H1.15 (D0), U3L1.15 (D0), U4H1.14 (D0), U4L1.14 (D0); also elsewhere on the board
/D_{1}: U3H1.16 (D1), U3L1.16 (D1), U4H1.16 (D1), U4L1.16 (D1); also elsewhere on the board
/D_{2}: U3H1.17 (D2), U3L1.17 (D2), U4H1.18 (D2), U4L1.18 (D2); also elsewhere on the board
/D_{3}: U3H1.19 (D3), U3L1.19 (D3), U4H1.20 (D3), U4L1.20 (D3); also elsewhere on the board
/D_{4}: U3H1.20 (D4), U3L1.20 (D4), U4H1.23 (D4), U4L1.23 (D4); also elsewhere on the board
/D_{5}: U3H1.21 (D5), U3L1.21 (D5), U4H1.25 (D5), U4L1.25 (D5); also elsewhere on the board
/D_{6}: U3H1.22 (D6), U3L1.22 (D6), U4H1.27 (D6), U4L1.27 (D6); also elsewhere on the board
/D_{7}: U3H1.23 (D7), U3L1.23 (D7), U4H1.29 (D7), U4L1.29 (D7); also elsewhere on the board
/ROM/ROM.~OE: SJ4.3 (B), SJ5.1 (A), U4H1.13 (~GVPP), U4L1.13 (~GVPP); also elsewhere on the board
/~RD: U3H1.24 (~CE), U3L1.24 (~CE), U4H1.11 (~CE), U4L1.11 (~CE); also elsewhere on the board
/~WR: SJ19.2 (C), TP1.1; also elsewhere on the board
GND: C3.2, C4.2, SJ17.1 (A), SJ18.1 (A), U3H1.18 (GND), U3L1.18 (GND), U4H1.12 (GND), U4H1.31 (GND), U4L1.12 (GND), U4L1.31 (GND); also elsewhere on the board
unnamed: SJ4.1 (A), SJ5.3 (B), SJ6.2 (C)
unnamed: SJ4.2 (C), U3H1.26 (A16), U3L1.26 (A16)
unnamed: SJ5.2 (C), U3H1.33 (~OE), U3L1.33 (~OE)
unnamed: SJ17.2 (C), U4L1.32 (A20)
unnamed: SJ18.2 (C), U4H1.32 (A20)
unnamed: SJ19.1 (A), TP2.1
unnamed: SJ19.3 (B), TP3.1

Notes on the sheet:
LOROM
SNES MASK
/~{BYTE}
HIROM
EPROM
LOROM HIROM

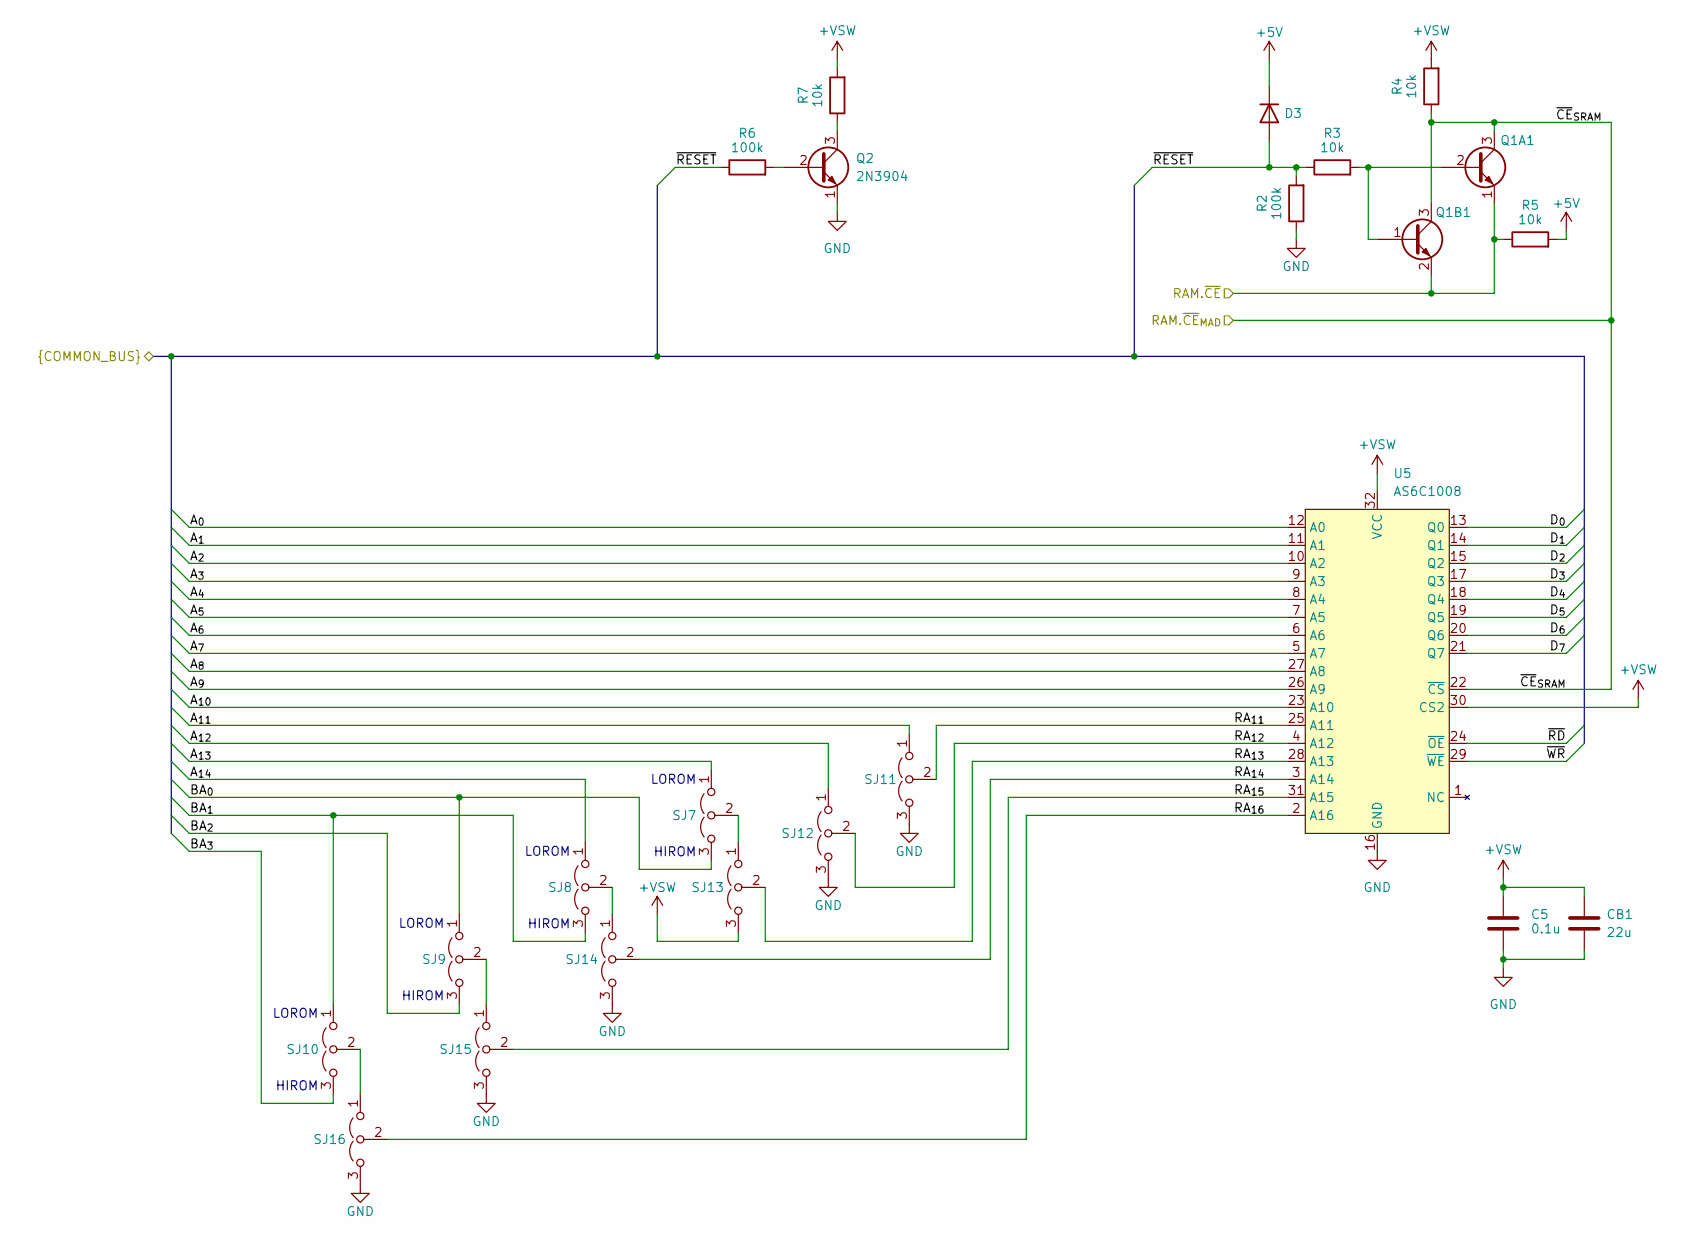
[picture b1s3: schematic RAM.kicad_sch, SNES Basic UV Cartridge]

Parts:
C5: 0.1u; C_THT
CB1: 22u; CP_Radial_D5.0mm_P2.50mm
D3: D; DIODE_THT_SMT
Q1A1, Q2: 2N3904; TO-92L_Inline_Wide
Q1B1: MMBT3904; SOT-23
R2, R6: 100k; THT_SMT_0803
R3, R4, R5, R7: 10k; THT_SMT_0803
SJ7, SJ8, SJ9, SJ10, SJ11, SJ12, SJ13, SJ14, SJ15, SJ16: Jumper_3_Open; SJ_2
U5: AS6C1008; DIP-32_W15.24mm

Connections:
+5V: D3.1 (K), R5.2; also elsewhere on the board
+VSW: C5.1, CB1.1, R4.2, R7.2, SJ13.3 (B), U5.30 (CS2), U5.32 (VCC); also elsewhere on the board
/A_{0}: U5.12 (A0); also elsewhere on the board
/A_{1}: U5.11 (A1); also elsewhere on the board
/A_{2}: U5.10 (A2); also elsewhere on the board
/A_{3}: U5.9 (A3); also elsewhere on the board
/A_{4}: U5.8 (A4); also elsewhere on the board
/A_{5}: U5.7 (A5); also elsewhere on the board
/A_{6}: U5.6 (A6); also elsewhere on the board
/A_{7}: U5.5 (A7); also elsewhere on the board
/A_{8}: U5.27 (A8); also elsewhere on the board
/A_{9}: U5.26 (A9); also elsewhere on the board
/A_{10}: U5.23 (A10); also elsewhere on the board
/A_{11}: SJ11.1 (A); also elsewhere on the board
/A_{12}: SJ12.1 (A); also elsewhere on the board
/A_{13}: SJ7.1 (A); also elsewhere on the board
/A_{14}: SJ8.1 (A); also elsewhere on the board
/BA_{0}: SJ7.3 (B), SJ9.1 (A); also elsewhere on the board
/BA_{1}: SJ8.3 (B), SJ10.1 (A); also elsewhere on the board
/BA_{2}: SJ9.3 (B); also elsewhere on the board
/BA_{3}: SJ10.3 (B); also elsewhere on the board
/D_{0}: U5.13 (Q0); also elsewhere on the board
/D_{1}: U5.14 (Q1); also elsewhere on the board
/D_{2}: U5.15 (Q2); also elsewhere on the board
/D_{3}: U5.17 (Q3); also elsewhere on the board
/D_{4}: U5.18 (Q4); also elsewhere on the board
/D_{5}: U5.19 (Q5); also elsewhere on the board
/D_{6}: U5.20 (Q6); also elsewhere on the board
/D_{7}: U5.21 (Q7); also elsewhere on the board
/RAM/RAM.~CE: Q1A1.1 (E), Q1B1.2 (E), R5.1; also elsewhere on the board
/RAM/RA_{11}: SJ11.2 (C), U5.25 (A11)
/RAM/RA_{12}: SJ12.2 (C), U5.4 (A12)
/RAM/RA_{13}: SJ13.2 (C), U5.28 (A13)
/RAM/RA_{14}: SJ14.2 (C), U5.3 (A14)
/RAM/RA_{15}: SJ15.2 (C), U5.31 (A15)
/RAM/RA_{16}: SJ16.2 (C), U5.2 (A16)
/RAM/~CE_{SRAM}: Q1A1.3 (C), Q1B1.3 (C), R4.1, U5.22 (~CS); also elsewhere on the board
/~RD: U5.24 (~OE); also elsewhere on the board
/~RESET: D3.2 (A), R2.2, R3.1, R6.1; also elsewhere on the board
/~WR: U5.29 (~WE); also elsewhere on the board
GND: C5.2, CB1.2, Q2.1 (E), R2.1, SJ11.3 (B), SJ12.3 (B), SJ14.3 (B), SJ15.3 (B), SJ16.3 (B), U5.16 (GND); also elsewhere on the board
unnamed: Q1A1.2 (B), Q1B1.1 (B), R3.2
unnamed: Q2.2 (B), R6.2
unnamed: Q2.3 (C), R7.1
unnamed: SJ10.2 (C), SJ16.1 (A)
unnamed: SJ7.2 (C), SJ13.1 (A)
unnamed: SJ8.2 (C), SJ14.1 (A)
unnamed: SJ9.2 (C), SJ15.1 (A)

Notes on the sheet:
LOROM HIROM

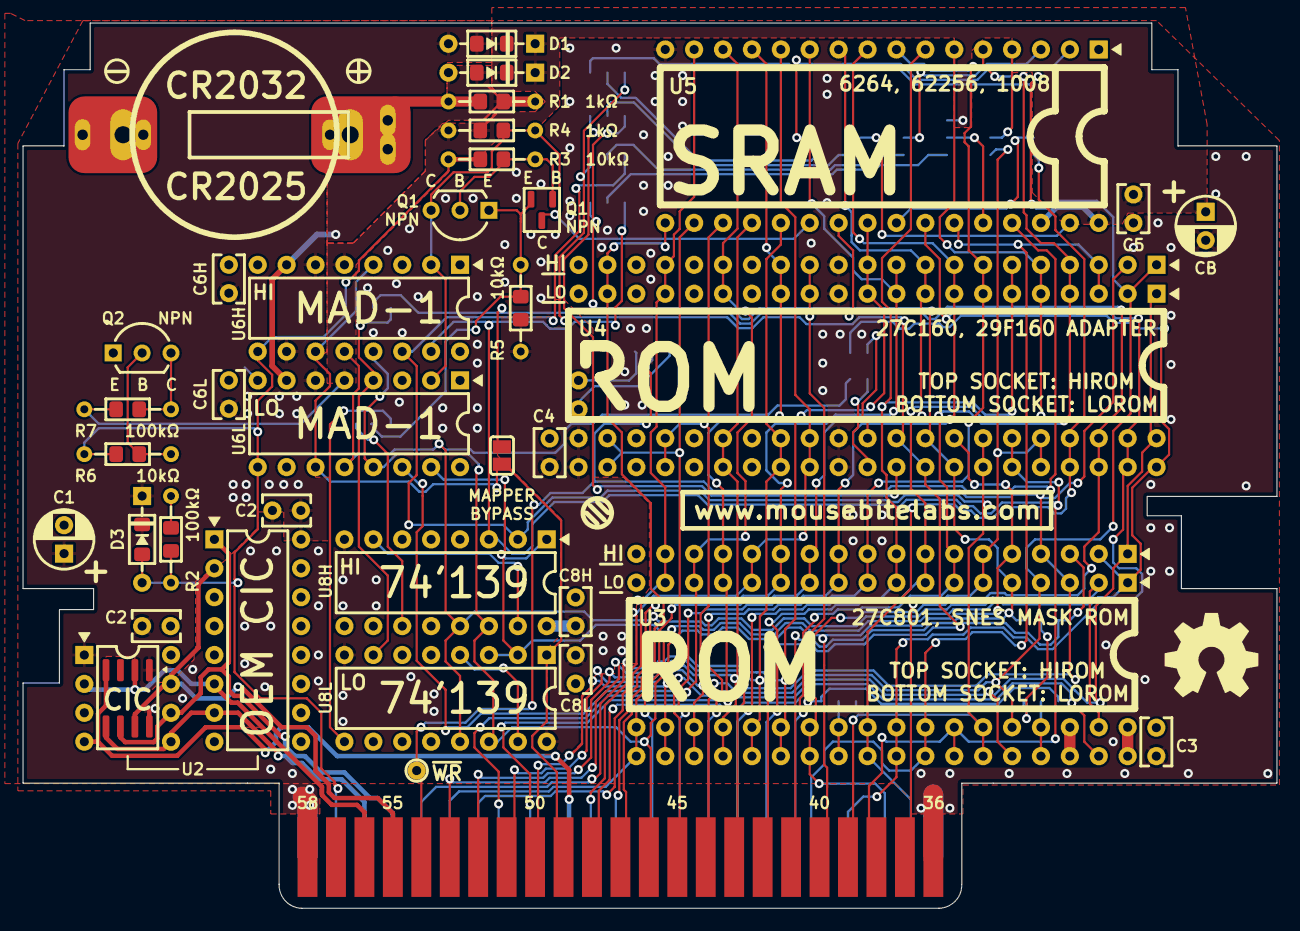
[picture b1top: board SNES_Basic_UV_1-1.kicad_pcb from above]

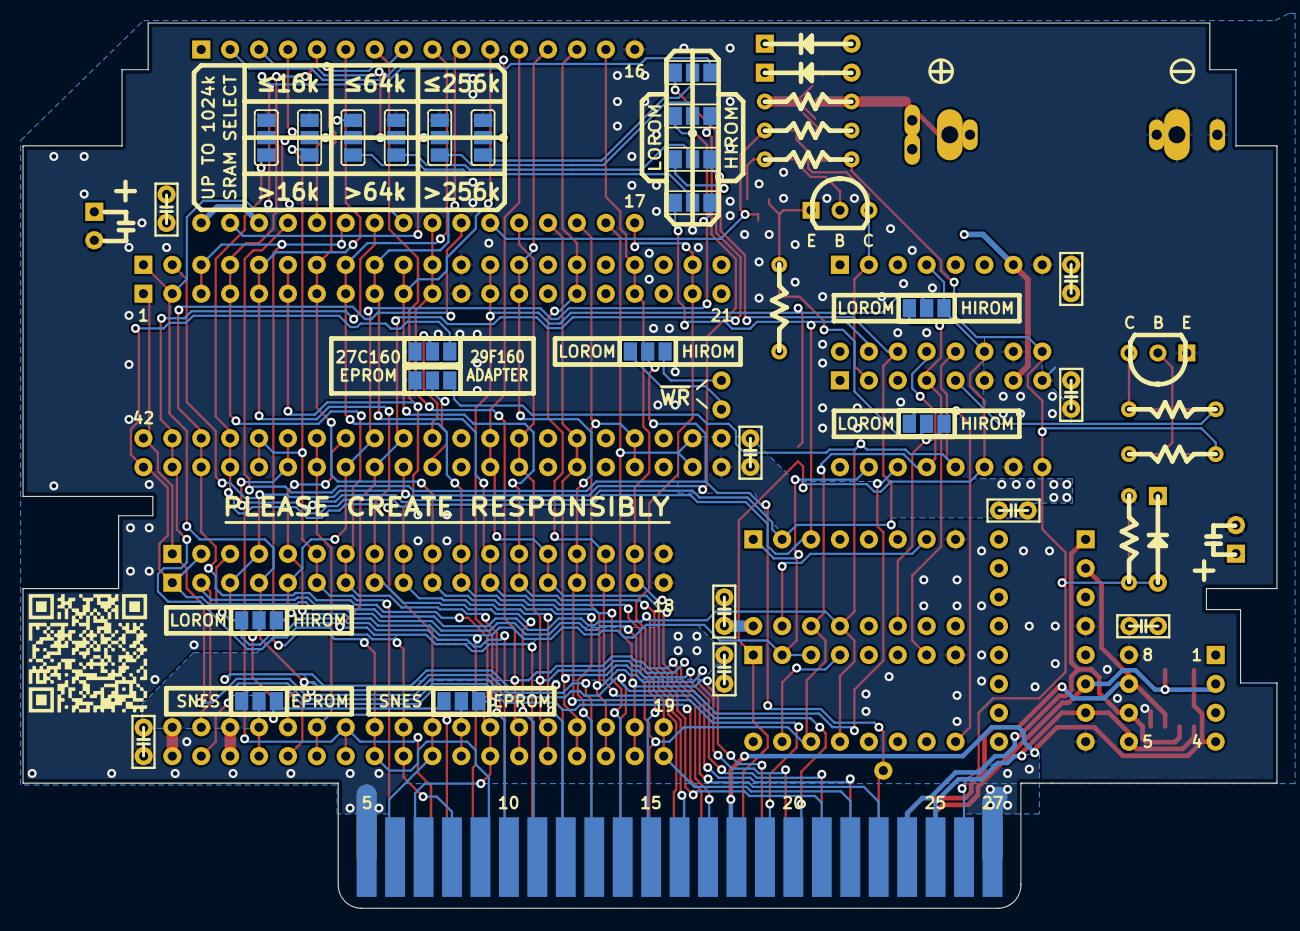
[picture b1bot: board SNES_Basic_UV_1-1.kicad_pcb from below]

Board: 2 copper layers, 110.2 x 77.8 mm, 60 parts (18 on the bottom side), 74 nets.

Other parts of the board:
C2#2, C6H, C6L, C8H, C8L: 0.1u; C_THT
CB: 22u; CP_Radial_D5.0mm_P2.50mm

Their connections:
+5V: C2#2.1, C6H.1, C6L.1, C8H.1, C8L.1; also elsewhere on the board
+VSW: CB.1; also elsewhere on the board
GND: C2#2.2, C6H.2, C6L.2, C8H.2, C8L.2, CB.2; also elsewhere on the board

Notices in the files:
Advanced UV/README.md:
©MouseBiteLabs 2025
